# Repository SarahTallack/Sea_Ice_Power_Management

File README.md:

# Sea Ice Power Management

## Overview: 

The below extract is from the vacwork advertisement: 

“This work feeds into the physical characterisation of sea ice using LiDAR and cameras to improve parameterisation of Earth System Models. A preliminary prototype rig was constructed for the SCALE Winter 2022 cruise to collect data from a Livox AVIA LiDAR (https://www.livoxtech.com/avia) and an Intel Realsense D455 Depth camera (https://www.intelrealsense.com/depth-camera-d455). During the SCALE cruise we were able to collect a comprehensive LiDAR/Realsense scan dataset of individual pancake ice floes which were collected and placed on deck. The goal of these vacation work positions is to improve the reliability and usability of the imaging rig to make it more robust for future experiments and cruises.” 

This project focuses on the design and improvement of the power management for the rig mentioned in the above. This report aims to outline the process taken to understand the power requirements of the system, as well as to research possible methods for supplying power in cold weather (-20°C). 

## Design Process and Decisions 

Before exploring methods for supplying power, it is important to understand the power requirements of the system. Thus, the first step is to research individual components and determine what voltages they are able to operate at and draw up a power budget for the system. The power budget for the system is shown in the following section. 

Once a power budget had been compiled, a meeting was had to discuss the best methods for supplying power to the system. It was decided that a battery supply such a EcoFlow or Jackery would be the most robust and allow other groups to use the supply if needed. Since these batteries are Lithium-Ion, which operate best at room-temperature, a temperature controller enclosure needs to be designed for the battery. Additionally, the team wanted the system to be able to be powered from mains or from the battery, and to be able to easily switch between these two options. 

Thus, two separate circuits need to be designed. The first should be able to distribute a single supply to at least two devices, as well as to switch between either mains or a battery as the power supply. The second design needed to control the temperature of the box, using a microcontroller, sensors and heating pads. 

## Power Budget

The power budget can be found in an excel spreadsheet called PowerBudget.

## Power Distribution

### Basic Operation

Two devices needed to be power by a single source, namely an Intel NUC (mini-PC) and a Livox AVIA. These devices needed to either be powered by a main supply, via an AC/DC supply, or by a DC output from a battery supply. 

The user should be able to switch between the two supplies and turn everything off. A panel mounted switch is to be connected via the switch header pins (J6). An external LED indicator is connected in a similar fashion, using the J7 pins.  

A MOSFET configuration is used for switching when power is supplied, and the switch is ON. When Q1 is turned on, it allows Q2 to be turned on, which then provides power to the external jacks. Fuses are added to the output of each supply. 

Component Selection 

The input jacks had to be selected to ensure they could withstand up to 8A. 8A fuses are placed to ensure the circuit is not overloaded. Schottky diodes are chosen that can withstand the current to be supplied. 

N-channel MOSFETs are chosen for low current switching, and the P-channel MOSFET is selected as it can withstand high currents. The DC jacks at the output are selected to withstand up to 5A of current, which is the maximum current draw of the devices to be powered. 

### KiCAD project files

The project files for this board can be found in "\PCB Design\Power Distribution".

## Temperature Controller

### Basic Operation

The PCB is designed to fit onto an STM32 Nucleo-64 microcontroller. It is designed to read a temperature controller and implement a bang-bang controller to maintain the ambient temperature in an enclosure between a lower and upper temperature value, by switching external heating pads on or off.  

An RTD sensor is used in a Wheatstone bridge configuration, and the two outputs of the bridge are sent into an instrumentation amplifier (U1). The output of the instrumentation amplifier is sent to an ADC pin on the Nucleo. The Nucleo then converts this ADC value into a temperature. Depending on this temperature value, the heaters are either turned on or off.  

A GPIO output pin is used in conjunction with a MOSFET switching circuit, to supply an external power source to the heating pads, as the pads could not be powered by the microcontroller. 

A pushbutton is used to turn on and off the control, and an indicator is used to show if the system is operational or not.  

### KiCAD project files

The project files for this board can be found in "\PCB Design\Temperature Controller".

### STM Nucleo-64 Code

The code used for the temperature controller can be found in "\Temperature Control Code\TemperatureController".

## Component Selection and Calculations
Most calculations were done using the TemperatureSensorValues.mlx file. 

## Assembly and Testing of boards

## Other components needed

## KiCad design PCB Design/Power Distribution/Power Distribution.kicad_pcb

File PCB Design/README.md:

# Sea Ice Power Management

## Getting started

To make it easy for you to get started with GitLab, here's a list of recommended next steps.

Already a pro? Just edit this README.md and make it your own. Want to make it easy? [Use the template at the bottom](#editing-this-readme)!

## Add your files

- [ ] [Create](https://docs.gitlab.com/ee/user/project/repository/web_editor.html#create-a-file) or [upload](https://docs.gitlab.com/ee/user/project/repository/web_editor.html#upload-a-file) files
- [ ] [Add files using the command line](https://docs.gitlab.com/ee/gitlab-basics/add-file.html#add-a-file-using-the-command-line) or push an existing Git repository with the following command:

```
cd existing_repo
git remote add origin https://gitlab.com/sarahtallack/sea-ice-power-management.git
git branch -M main
git push -uf origin main
```

## Integrate with your tools

- [ ] [Set up project integrations](https://gitlab.com/sarahtallack/sea-ice-power-management/-/settings/integrations)

## Collaborate with your team

- [ ] [Invite team members and collaborators](https://docs.gitlab.com/ee/user/project/members/)
- [ ] [Create a new merge request](https://docs.gitlab.com/ee/user/project/merge_requests/creating_merge_requests.html)
- [ ] [Automatically close issues from merge requests](https://docs.gitlab.com/ee/user/project/issues/managing_issues.html#closing-issues-automatically)
- [ ] [Enable merge request approvals](https://docs.gitlab.com/ee/user/project/merge_requests/approvals/)
- [ ] [Automatically merge when pipeline succeeds](https://docs.gitlab.com/ee/user/project/merge_requests/merge_when_pipeline_succeeds.html)

## Test and Deploy

Use the built-in continuous integration in GitLab.

- [ ] [Get started with GitLab CI/CD](https://docs.gitlab.com/ee/ci/quick_start/index.html)
- [ ] [Analyze your code for known vulnerabilities with Static Application Security Testing(SAST)](https://docs.gitlab.com/ee/user/application_security/sast/)
- [ ] [Deploy to Kubernetes, Amazon EC2, or Amazon ECS using Auto Deploy](https://docs.gitlab.com/ee/topics/autodevops/requirements.html)
- [ ] [Use pull-based deployments for improved Kubernetes management](https://docs.gitlab.com/ee/user/clusters/agent/)
- [ ] [Set up protected environments](https://docs.gitlab.com/ee/ci/environments/protected_environments.html)

***

# Editing this README

When you're ready to make this README your own, just edit this file and use the handy template below (or feel free to structure it however you want - this is just a starting point!). Thank you to [makeareadme.com](https://www.makeareadme.com/) for this template.

## Suggestions for a good README
Every project is different, so consider which of these sections apply to yours. The sections used in the template are suggestions for most open source projects. Also keep in mind that while a README can be too long and detailed, too long is better than too short. If you think your README is too long, consider utilizing another form of documentation rather than cutting out information.

## Name
Choose a self-explaining name for your project.

## Description
Let people know what your project can do specifically. Provide context and add a link to any reference visitors might be unfamiliar with. A list of Features or a Background subsection can also be added here. If there are alternatives to your project, this is a good place to list differentiating factors.

## Badges
On some READMEs, you may see small images that convey metadata, such as whether or not all the tests are passing for the project. You can use Shields to add some to your README. Many services also have instructions for adding a badge.

## Visuals
Depending on what you are making, it can be a good idea to include screenshots or even a video (you'll frequently see GIFs rather than actual videos). Tools like ttygif can help, but check out Asciinema for a more sophisticated method.

## Installation
Within a particular ecosystem, there may be a common way of installing things, such as using Yarn, NuGet, or Homebrew. However, consider the possibility that whoever is reading your README is a novice and would like more guidance. Listing specific steps helps remove ambiguity and gets people to using your project as quickly as possible. If it only runs in a specific context like a particular programming language version or operating system or has dependencies that have to be installed manually, also add a Requirements subsection.

## Usage
Use examples liberally, and show the expected output if you can. It's helpful to have inline the smallest example of usage that you can demonstrate, while providing links to more sophisticated examples if they are too long to reasonably include in the README.

## Support
Tell people where they can go to for help. It can be any combination of an issue tracker, a chat room, an email address, etc.

## Roadmap
If you have ideas for releases in the future, it is a good idea to list them in the README.

## Contributing
State if you are open to contributions and what your requirements are for accepting them.

For people who want to make changes to your project, it's helpful to have some documentation on how to get started. Perhaps there is a script that they should run or some environment variables that they need to set. Make these steps explicit. These instructions could also be useful to your future self.

You can also document commands to lint the code or run tests. These steps help to ensure high code quality and reduce the likelihood that the changes inadvertently break something. Having instructions for running tests is especially helpful if it requires external setup, such as starting a Selenium server for testing in a browser.

## Authors and acknowledgment
Show your appreciation to those who have contributed to the project.

## License
For open source projects, say how it is licensed.

## Project status
If you have run out of energy or time for your project, put a note at the top of the README saying that development has slowed down or stopped completely. Someone may choose to fork your project or volunteer to step in as a maintainer or owner, allowing your project to keep going. You can also make an explicit request for maintainers.

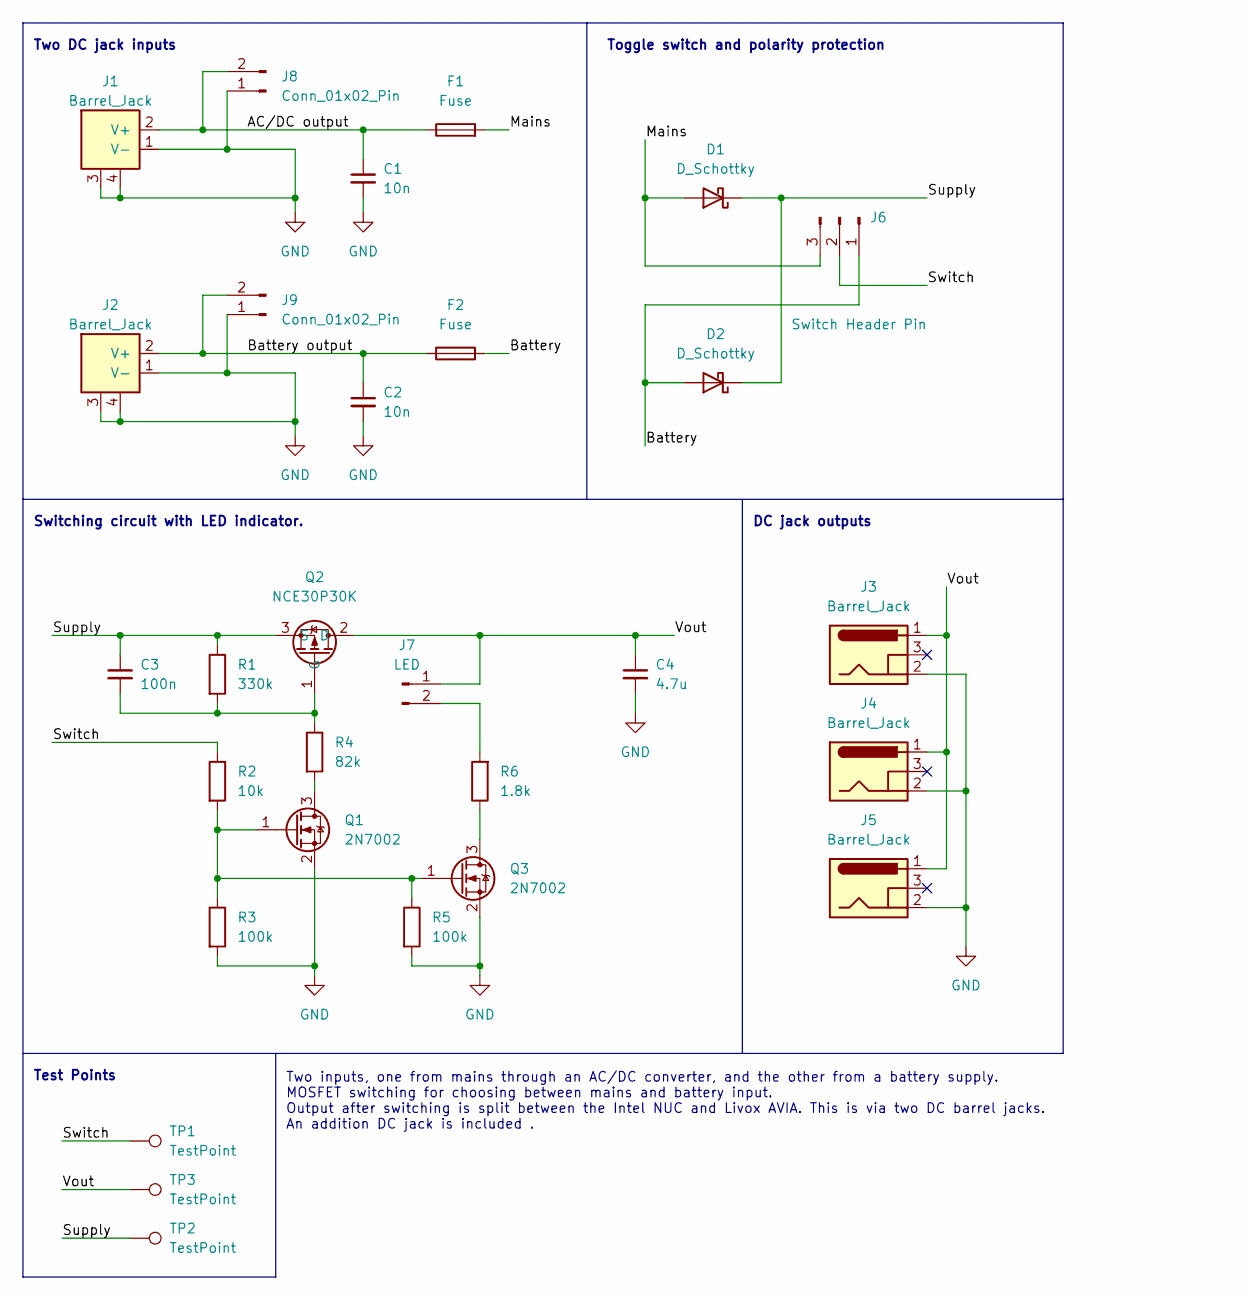
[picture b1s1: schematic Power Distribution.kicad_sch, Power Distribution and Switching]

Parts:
C1, C2: 10n; C_0402_1005Metric; LCSC C15195
C3: 100n; C_0402_1005Metric; LCSC C307331
C4: 4.7u; C_1206_3216Metric; LCSC C29823
D1, D2: D_Schottky; Schottky Diode SK1010C; LCSC C65020
F1, F2: Fuse; FUSE Holder ROHS; LCSC C3131
J1, J2: Barrel_Jack; CONN-TH_XT60PW-M; LCSC C98732
J3, J4, J5: Barrel_Jack; DC Jack 5A; LCSC C388625
J6: Switch Header Pin; PinHeader_1x03_P2.54mm_Vertical
J7: LED; 2 Pin Male Header
J8, J9: Conn_01x02_Pin; PinHeader_1x02_P2.54mm_Vertical
Q1, Q3: 2N7002; SOT-23; LCSC C8545
Q2: NCE30P30K; TO-252-2; LCSC C130106
R1: 330k; R_0402_1005Metric; LCSC C25778
R2: 10k; R_0402_1005Metric; LCSC C25744
R3, R5: 100k; R_0402_1005Metric; LCSC C25741
R4: 82k; R_0805_2012Metric; LCSC C17840
R6: 1.8k; R_0805_2012Metric; LCSC C17398
TP1, TP2, TP3: TestPoint; TestPoint_THTPad_D1.0mm_Drill0.5mm

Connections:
/AC/DC output: C1.1, F1.1, J1.2 (V+), J8.2
/Battery: D2.2 (A), F2.2, J6.1
/Battery output: C2.1, F2.1, J2.2 (V+), J9.2
/Mains: D1.2 (A), F1.2, J6.3
/Supply: C3.1, D1.1 (K), D2.1 (K), Q2.3 (S), R1.1, TP2.1
/Switch: J6.2, R2.1, TP1.1
/Vout: C4.1, J3.1, J4.1, J5.1, J7.1, Q2.2 (D), TP3.1
GND: C1.2, C2.2, C4.2, J1.1 (V-), J1.3, J1.4, J2.1 (V-), J2.3, J2.4, J3.2, J4.2, J5.2, J8.1, J9.1, Q1.2 (S), Q3.2 (S), R3.2, R5.2
unnamed: J7.2, R6.2
unnamed: Q1.3 (D), R4.2
unnamed: Q1.1 (G), Q3.1 (G), R2.2, R3.1, R5.1
unnamed: C3.2, Q2.1 (G), R1.2, R4.1
unnamed: Q3.3 (D), R6.1

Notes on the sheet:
Toggle switch and polarity protection
Two inputs, one from mains through an AC/DC converter, and the other from a battery supply. MOSFET switching for choosing between mains and battery input. Output after switching is split between the Intel NUC and Livox AVIA. This is via two DC barrel jacks. An addition DC jack is included .
Test Points
Switching circuit with LED indicator.
DC jack outputs
Two DC jack inputs

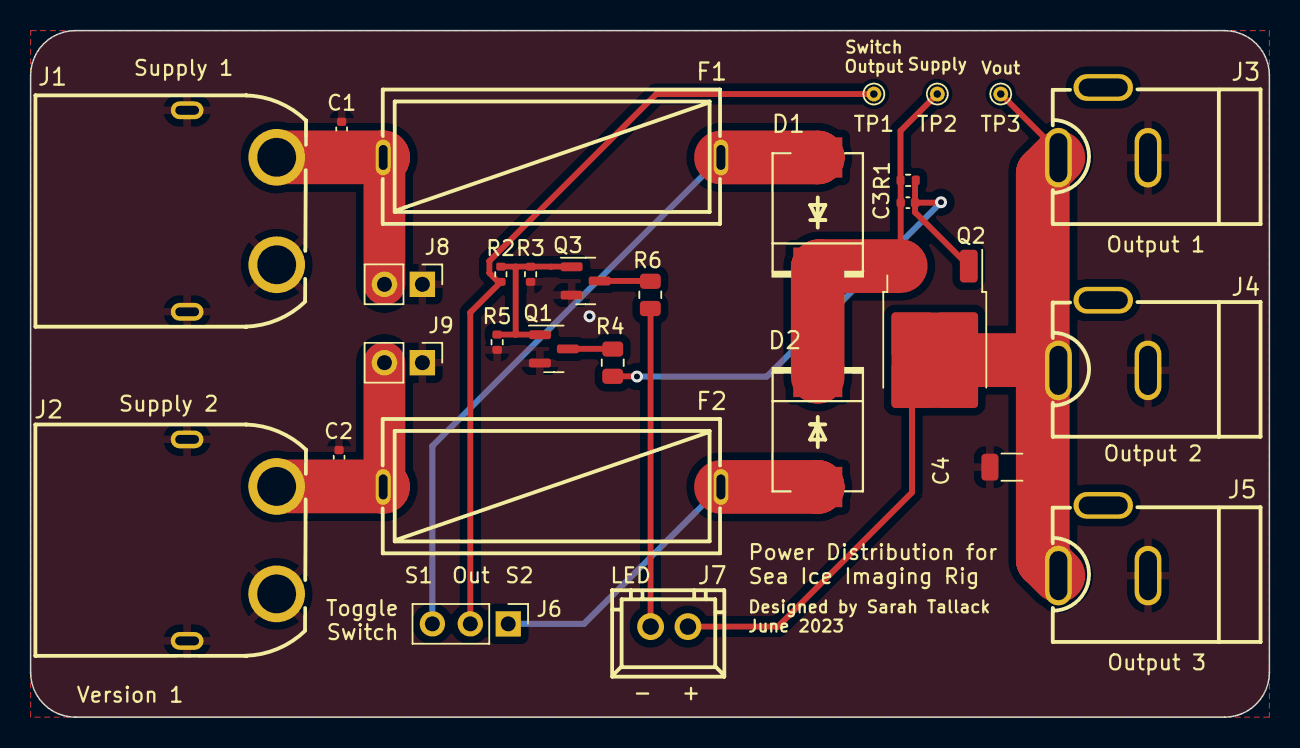
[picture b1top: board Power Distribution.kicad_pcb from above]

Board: 2 copper layers, 83.0 x 46.0 mm, 29 parts (0 on the bottom side), 13 nets.

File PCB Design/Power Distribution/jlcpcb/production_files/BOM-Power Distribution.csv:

Comment,Designator,Footprint,LCSC
NCE30P30K,Q2,TO-252-2,C130106
10n,"C1,C2",C_0402_1005Metric,C15195
1.8k,R6,R_0805_2012Metric,C17398
82k,R4,R_0805_2012Metric,C17840
LED,J7,2 Pin Male Header,C20079
Switch Header Pin,J6,PinHeader_1x03_P2.54mm_Vertical,C20547
100k,"R3,R5",R_0402_1005Metric,C25741
10k,R2,R_0402_1005Metric,C25744
330k,R1,R_0402_1005Metric,C25778
4.7u,C4,C_1206_3216Metric,C29823
100n,C3,C_0402_1005Metric,C307331
Fuse,"F1,F2",FUSE Holder ROHS,C3131
Barrel_Jack,"J3,J4,J5",DC Jack 5A,C388625
D_Schottky,"D1,D2",Schottky Diode SK1010C,C65020
2N7002,"Q1,Q3",SOT-23,C8545
Barrel_Jack,"J1,J2",CONN-TH_XT60PW-M,C98732
TestPoint,TP1,TestPoint_THTPad_D1.0mm_Drill0.5mm,
TestPoint,TP2,TestPoint_THTPad_D1.0mm_Drill0.5mm,
TestPoint,TP3,TestPoint_THTPad_D1.0mm_Drill0.5mm,
Conn_01x02_Pin,J8,PinHeader_1x02_P2.54mm_Vertical,
Conn_01x02_Pin,J9,PinHeader_1x02_P2.54mm_Vertical,

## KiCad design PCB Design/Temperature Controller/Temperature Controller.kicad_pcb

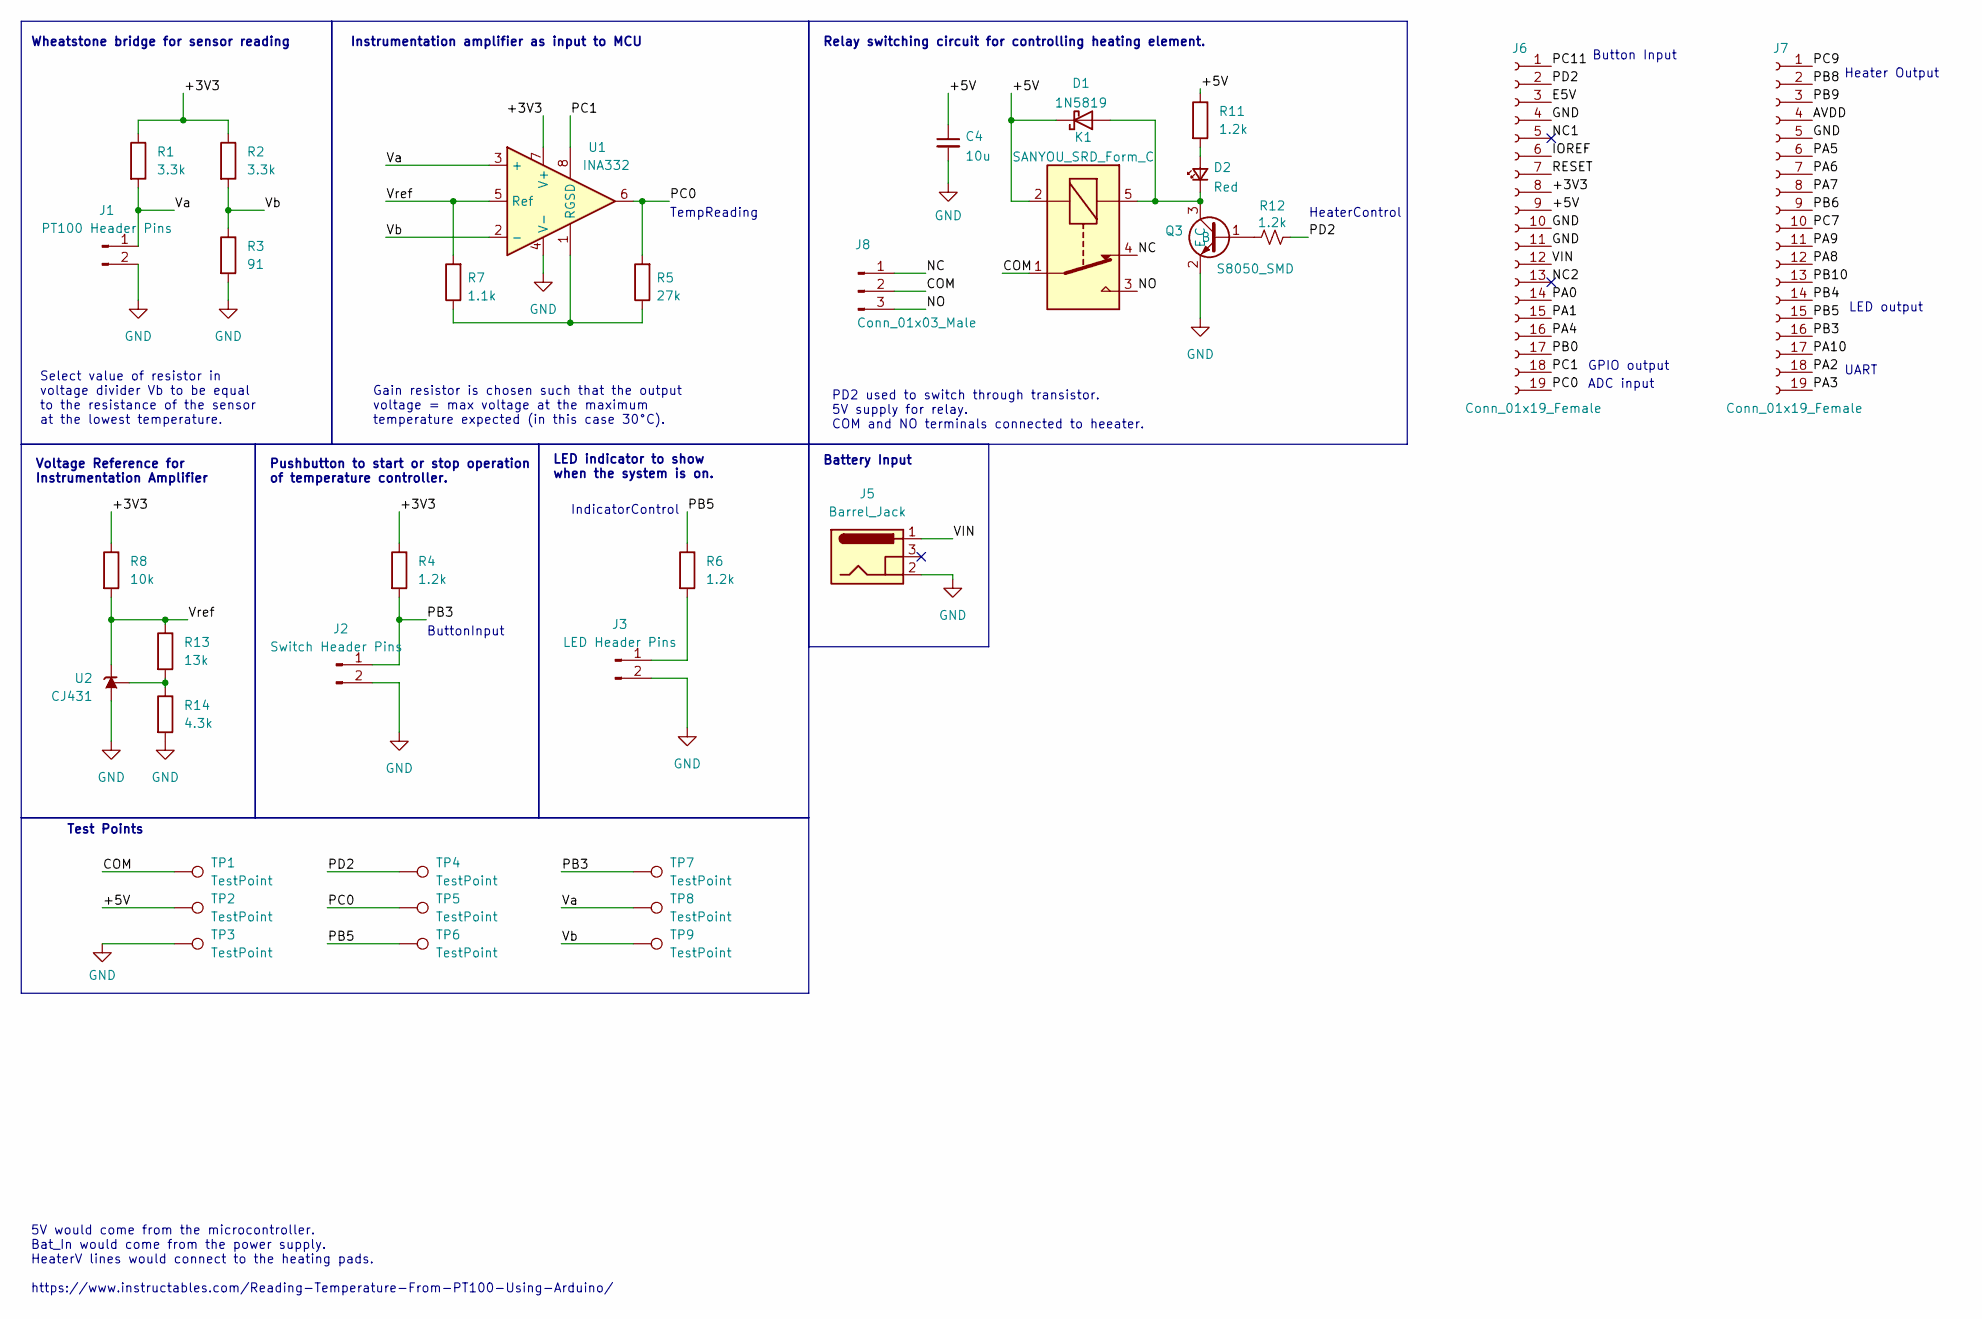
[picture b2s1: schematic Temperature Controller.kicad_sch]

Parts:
C4: 10u; C_0603_1608Metric; LCSC C96446
D1: 1N5819; D_SOD-123; LCSC C8598
D2: Red; D_0603_1608Metric; LCSC C2286
J1: PT100 Header Pins; 2 Pin Male Header; LCSC C20079
J2: Switch Header Pins; 2 Pin Male Header; LCSC C20079
J3: LED Header Pins; 2 Pin Male Header; LCSC C20079
J5: Barrel_Jack; DC Jack 5A; LCSC C388625
J6, J7: Conn_01x19_Female; PinSocket_1x19_P2.54mm_Vertical
J8: Conn_01x03_Male; TerminalBlock_Altech_AK300-3_P5.00mm; LCSC C72334
K1: SANYOU_SRD_Form_C; Relay_SPDT_SANYOU_SRD_Series_Form_C; LCSC C35449
Q3: S8050_SMD; SOT-23; LCSC C2146
R1, R2: 3.3k; R_0603_1608Metric; LCSC C22978
R3: 91; R_0603_1608Metric; LCSC C2960792
R4, R6, R11, R12: 1.2k; R_0603_1608Metric; LCSC C22765
R5: 27k; R_0603_1608Metric; LCSC C22967
R7: 1.1k; R_0603_1608Metric; LCSC C22764
R8: 10k; R_0603_1608Metric; LCSC C25804
R13: 13k; R_0603_1608Metric; LCSC C22797
R14: 4.3k; R_0603_1608Metric; LCSC C23159
TP1, TP2, TP3, TP4, TP5, TP6, TP7: TestPoint; TestPoint_THTPad_D1.0mm_Drill0.5mm
TP8, TP9: TestPoint; TestPoint_Pad_D1.5mm
U1: INA332; VSSOP-8_3.0x3.0mm_P0.65mm; LCSC C181461
U2: CJ431; SOT-23; LCSC C171428

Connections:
/+3V3: J6.8, R1.1, R2.1, R4.1, R8.1, U1.7 (V+)
/+5V: C4.1, D1.1 (K), J6.9, K1.2, R11.1, TP2.1
/AVDD: J7.4
/COM: J8.2, K1.1, TP1.1
/E5V: J6.3
/IOREF: J6.6
/NC: J8.1, K1.4
/NC1: J6.5
/NC2: J6.13
/NO: J8.3, K1.3
/PA0: J6.14
/PA1: J6.15
/PA2: J7.18
/PA3: J7.19
/PA4: J6.16
/PA5: J7.6
/PA6: J7.7
/PA7: J7.8
/PA8: J7.12
/PA9: J7.11
/PA10: J7.17
/PB0: J6.17
/PB3: J2.1, J7.16, R4.2, TP7.1
/PB4: J7.14
/PB5: J7.15, R6.1, TP6.1
/PB6: J7.9
/PB8: J7.2
/PB9: J7.3
/PB10: J7.13
/PC0: J6.19, R5.2, TP5.1, U1.6
/PC1: J6.18, U1.8 (SD)
/PC7: J7.10
/PC9: J7.1
/PC11: J6.1
/PD2: J6.2, R12.2, TP4.1
/RESET: J6.7
/VIN: J5.1, J6.12
/Va: J1.1, R1.2, TP8.1, U1.3 (+)
/Vb: R2.2, R3.1, TP9.1, U1.2 (-)
/Vref: R7.2, R8.2, R13.1, U1.5 (Ref), U2.2 (K)
GND: C4.2, J1.2, J2.2, J3.2, J5.2, J6.4, J6.10, J6.11, J7.5, Q3.2 (E), R3.2, R14.2, TP3.1, U1.4 (V-), U2.3 (A)
unnamed: D1.2 (A), D2.1 (K), K1.5, Q3.3 (C)
unnamed: D2.2 (A), R11.2
unnamed: J3.1, R6.2
unnamed: Q3.1 (B), R12.1
unnamed: R5.1, R7.1, U1.1 (RG)
unnamed: R13.2, R14.1, U2.1 (REF)

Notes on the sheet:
Select value of resistor in voltage divider Vb to be equal to the resistance of the sensor at the lowest temperature.
Relay switching circuit for controlling heating element.
Button Input
Heater Output
Test Points
Gain resistor is chosen such that the output voltage = max voltage at the maximum temperature expected (in this case 30°C).
Battery Input
Voltage Reference for Instrumentation Amplifier
ButtonInput
ADC input
LED indicator to show when the system is on.
5V would come from the microcontroller. Bat_In would come from the power supply. HeaterV lines would connect to the heating pads. https://www.instructables.com/Reading-Temperature-From-PT100-Using-Arduino/
PD2 used to switch through transistor. 5V supply for relay. COM and NO terminals connected to heeater.
GPIO output
Wheatstone bridge for sensor reading
HeaterControl
Pushbutton to start or stop operation of temperature controller.
TempReading
IndicatorControl
UART
Instrumentation amplifier as input to MCU
LED output

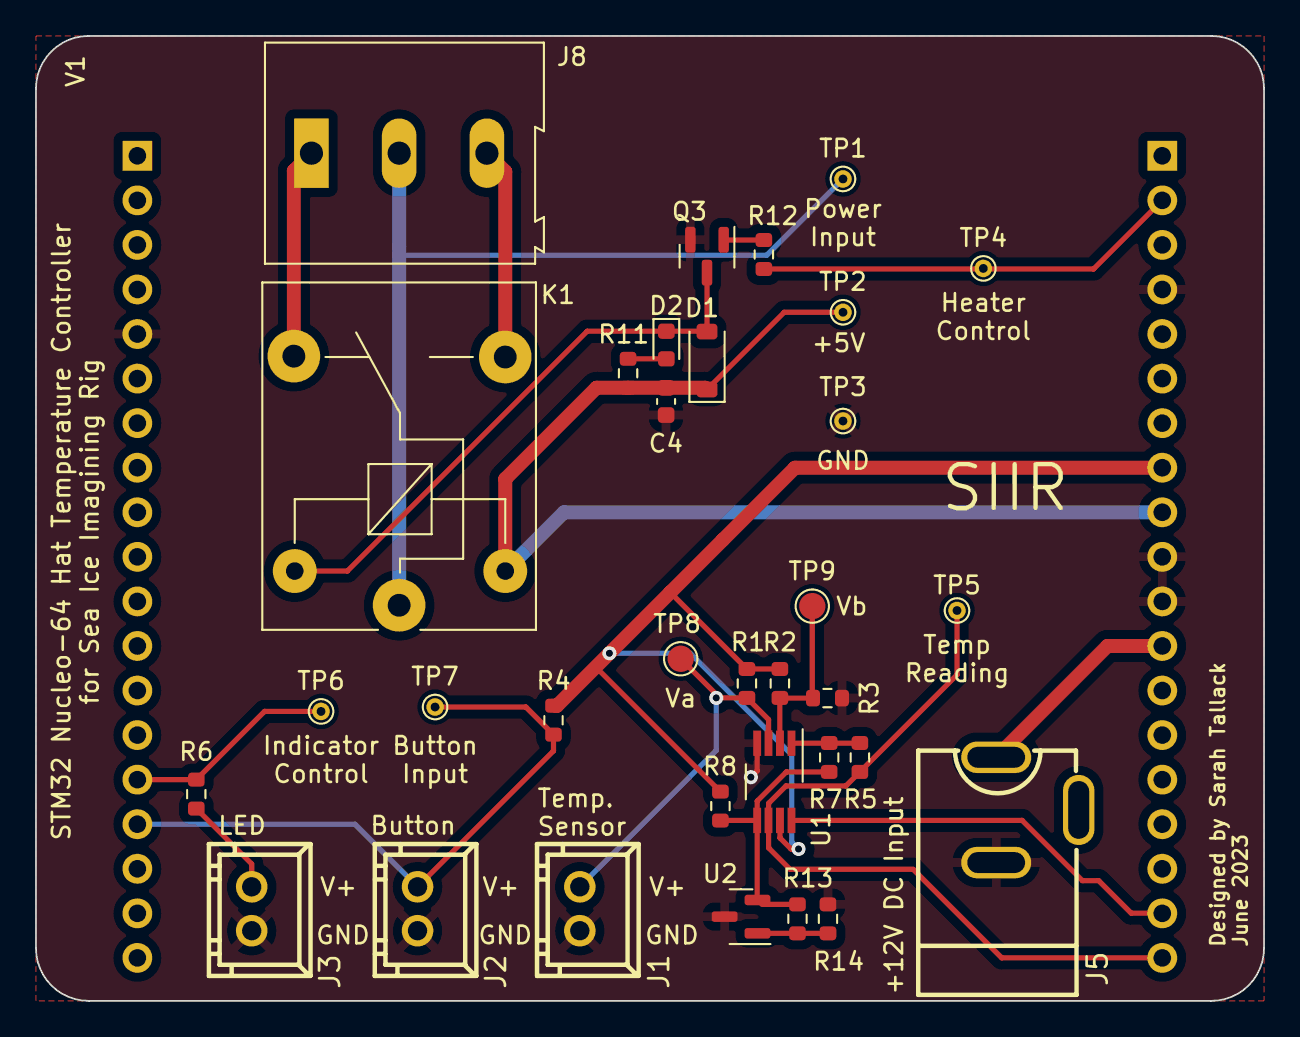
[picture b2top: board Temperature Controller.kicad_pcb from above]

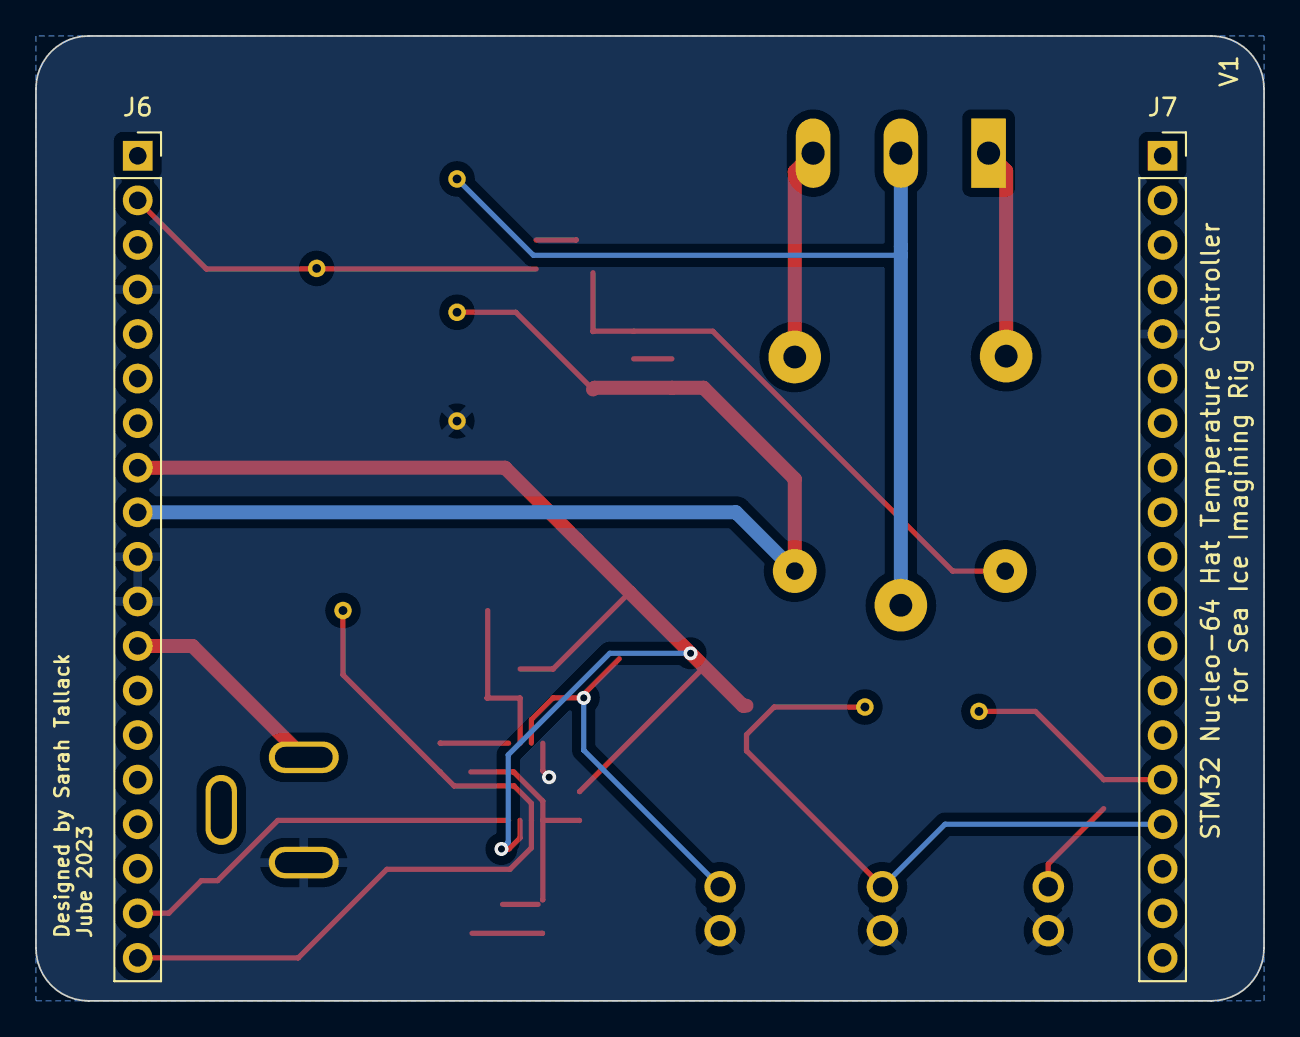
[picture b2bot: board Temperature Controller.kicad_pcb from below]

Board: 2 copper layers, 70.0 x 55.0 mm, 35 parts (2 on the bottom side), 21 nets.

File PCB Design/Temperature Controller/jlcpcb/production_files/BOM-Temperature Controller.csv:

Comment,Designator,Footprint,LCSC
CJ431,U2,SOT-23,C171428
INA332,U1,VSSOP-8_3.0x3.0mm_P0.65mm,C181461
PT100 Header Pins,"J1,J2,J3",2 Pin Male Header,C20079
S8050_SMD,Q3,SOT-23,C2146
1.1k,R7,R_0603_1608Metric,C22764
1.2k,"R12,R6",R_0603_1608Metric,C22765
Red,D2,D_0603_1608Metric,C2286
27k,R5,R_0603_1608Metric,C22967
3.3k,"R1,R2",R_0603_1608Metric,C22978
10k,R8,R_0603_1608Metric,C25804
91,R3,R_0603_1608Metric,C2960792
SANYOU_SRD_Form_C,K1,Relay_SPDT_SANYOU_SRD_Series_Form_C,C35449
Barrel_Jack,J5,DC Jack 5A,C388625
Conn_01x03_Male,J8,TerminalBlock_Altech_AK300-3_P5.00mm,C72334
1N5819,D1,D_SOD-123,C8598
10u,C4,C_0603_1608Metric,C96446
TestPoint,TP5,TestPoint_THTPad_D1.0mm_Drill0.5mm,
TestPoint,TP9,TestPoint_Pad_D1.5mm,
TestPoint,TP2,TestPoint_THTPad_D1.0mm_Drill0.5mm,
TestPoint,TP7,TestPoint_THTPad_D1.0mm_Drill0.5mm,
TestPoint,TP8,TestPoint_Pad_D1.5mm,
TestPoint,TP6,TestPoint_THTPad_D1.0mm_Drill0.5mm,
TestPoint,TP4,TestPoint_THTPad_D1.0mm_Drill0.5mm,
TestPoint,TP1,TestPoint_THTPad_D1.0mm_Drill0.5mm,
TestPoint,TP3,TestPoint_THTPad_D1.0mm_Drill0.5mm,
Conn_01x19_Female,J7,PinSocket_1x19_P2.54mm_Vertical,
Conn_01x19_Female,J6,PinSocket_1x19_P2.54mm_Vertical,

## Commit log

2023-03-29 Temp controller and power distribution PCBS and temp controller code
2023-03-29 Added power budget
2023-03-29 populated power budget
2023-03-29 testing procedure added
